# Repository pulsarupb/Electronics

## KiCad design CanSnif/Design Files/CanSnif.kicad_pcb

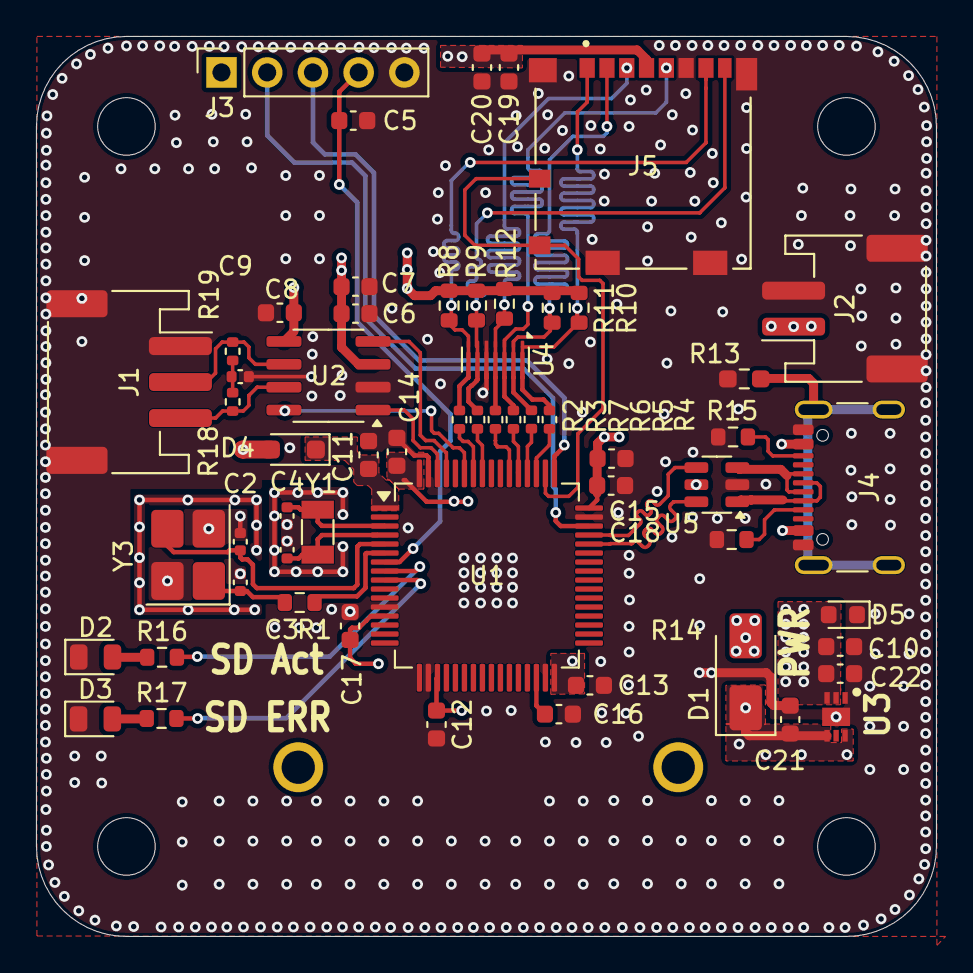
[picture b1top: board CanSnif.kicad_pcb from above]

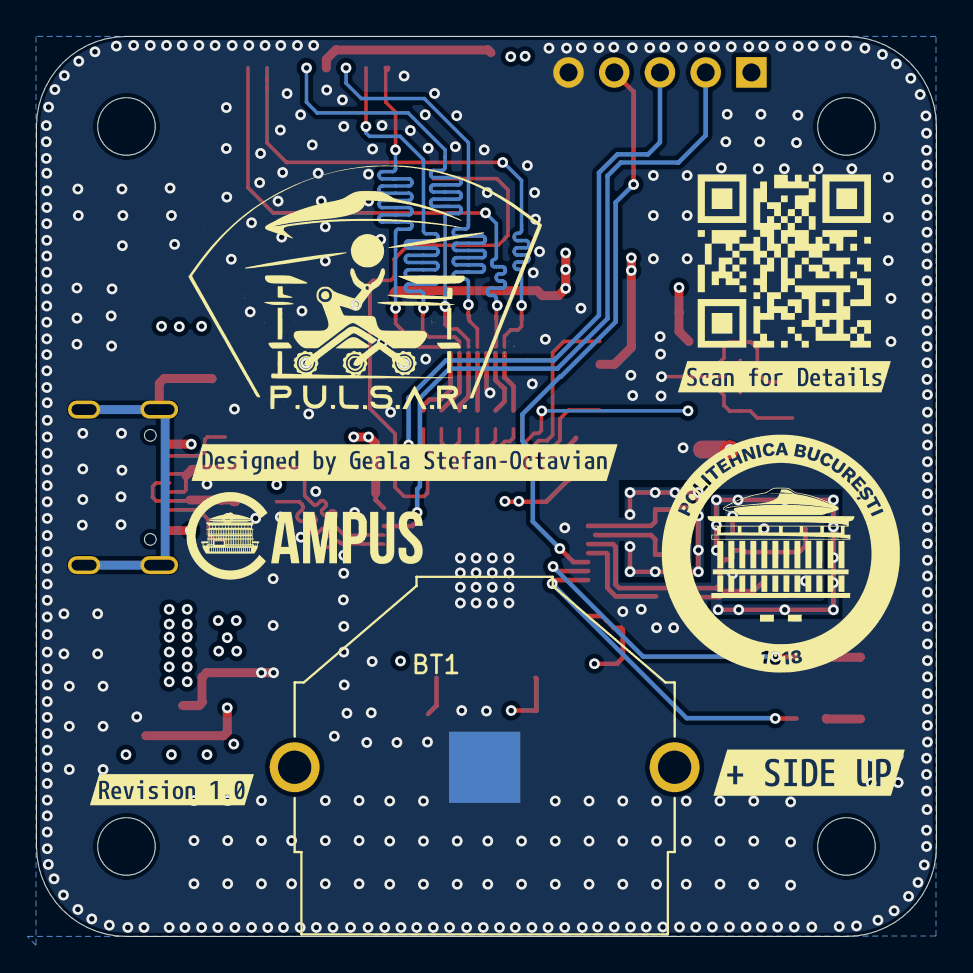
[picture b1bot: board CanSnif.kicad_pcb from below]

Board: 4 copper layers, 50.0 x 50.0 mm, 63 parts (5 on the bottom side), 44 nets.

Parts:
BT1: 3003; BAT_3003
C1, C2: 10pF; C_0402_1005Metric
C3, C4: 14pF; C_0402_1005Metric
C5, C6, C8, C11, C12, C13, C14, C17, C18, C20: 0.1uF; C_0603_1608Metric
C7, C10, C15, C19, C21, C22: 10uF; C_0603_1608Metric
C9: 4.7nF; C_0402_1005Metric
C16: 4.7uF; C_0603_1608Metric
D1: SS32; D_SMA
D2: SD Error; LED_0805_2012Metric
D3: SD Activity; LED_0805_2012Metric
D4: 1N5819WS; D_SOD-323_HandSoldering
D5: Red; LED_0603_1608Metric
J1: JST_XH; JST_PH_S3B-PH-SM4-TB_1x03-1MP_P2.00mm_Horizontal
J2: JST_XH; JST_PH_S2B-PH-SM4-TB_1x02-1MP_P2.00mm_Horizontal
J3: Pin_Header; PinSocket_1x05_P2.54mm_Vertical
J4: USB_C_Receptacle_USB2.0_16P; USB_C_Receptacle_GCT_USB4105-xx-A_16P_TopMnt_Horizontal
J5: 104031-0811; MOLEX_104031-0811
R1: 0; R_0603_1608Metric
R2, R3, R4, R5, R6, R7: 22; R_0402_1005Metric
R8, R9, R10, R11, R12: 47K; R_0603_1608Metric
R13: 200K; R_0603_1608Metric_Pad0.98x0.95mm_HandSolder
R14, R15: 5.1K; R_0603_1608Metric
R16, R17: 330; R_0603_1608Metric
R18, R19: 60; R_0402_1005Metric
U1: STM32U575RGT6; LQFP-64_10x10mm_P0.5mm
U2: TJA1051T-3; SOIC-8_3.9x4.9mm_P1.27mm
U3: LDL212PV33R; SON50P200X200X80-7N-D
U4: TPD6E05U06RVZ; Texas_R-PUSON-N14
U5: USBLC6-2SC6; SOT-23-6
Y1: 32.768KHz; Crystal_SMD_3215-2Pin_3.2x1.5mm
Y3: 16MHz; Crystal_SMD_3225-4Pin_3.2x2.5mm_HandSoldering
kibuzzard-69AC8A77: G***; kibuzzard-69AC8A77
kibuzzard-69AC84C5: G***; kibuzzard-69AC84C5
kibuzzard-69AC87A2: G***; kibuzzard-69AC87A2
kibuzzard-69AC8543: G***; kibuzzard-69AC8543

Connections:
+3V3: C8.1, C10.1, C12.1, C13.1, C14.1, C15.1, C17.1, C18.1, C19.2, C20.2, C22.1, D5.2, J3.1, J5.4 (VDD), R8.2, R9.2, R10.2, R11.2, R12.1, U1.13 (VDDA), U1.19 (VDD), U1.32 (VDD), U1.48 (VDDUSB), U1.64 (VDD), U2.5 (VIO), U3.2 (ADJ/SENSE), U3.3 (VOUT)
+5V: C6.2, C7.2, C21.1, D1.1 (K), U2.3 (VCC), U3.4 (VIN), U3.6 (EN)
CANH: J1.3, R18.2, U2.7 (CANH)
CANL: J1.2, R19.1, U2.6 (CANL)
CR2032: C11.2, D4.1 (K), U1.1 (VBAT)
FDCAN_RX: U1.61 (PB8), U2.4 (RXD)
FDCAN_S: U1.59 (PB7), U2.8 (S)
FDCAN_TX: U1.62 (PB9), U2.1 (TXD)
GND: BT1.N, C1.2, C2.2, C3.1, C4.1, C5.2, C6.1, C7.1, C8.2, C9.2, C10.2, C11.1, C12.2, C13.2, C14.2, C15.2, C16.2, C17.2, C18.2, C19.1, C20.1, C21.2, C22.2, D2.1 (K), D3.1 (K), D5.1, J1.1, J1.MP, J2.2, J2.MP, J3.5, J4.A1 (GND), J4.A12 (GND), J4.B1 (GND), J4.B12 (GND), J5.6 (VSS), J5.G1 (GND), J5.G2 (GND), J5.G3 (GND), J5.G4 (GND), R13.2, R14.2, R15.2, U1.12 (VSSA), U1.18 (VSS), U1.31 (VSS), U1.47 (VSS), U1.63 (VSS), U2.2 (GND), U3.1 (GND), U3.7 (EP), U4.5 (GND), U4.10 (GND), U5.2 (GND), Y3.2, Y3.4
NRST: C5.1, J3.4, U1.7 (NRST)
unnamed: C1.1, R1.1, Y3.1
unnamed: C9.1, R18.1, R19.2
unnamed: D1.2 (A), J2.1, J4.A4 (VBUS), J4.A9 (VBUS), J4.B4 (VBUS), J4.B9 (VBUS), U5.5 (VBUS)
unnamed: D2.2 (A), R16.1
unnamed: D3.2 (A), R17.1
unnamed: BT1.P1, BT1.P2, D4.2 (A)
unnamed: J4.A5 (CC1), R14.1
unnamed: J4.B5 (CC2), R15.1
unnamed: J4.A6 (D+), J4.B6 (D+), U5.3 (I/O2)
unnamed: J4.A7 (D-), J4.B7 (D-), U5.1 (I/O1)
unnamed: J4.S1 (SHIELD), R13.1
unnamed: J5.2 (CD/DAT3), R5.1, R11.1, U4.13 (D1-)
unnamed: J5.5 (CLK), R6.2
unnamed: J5.3 (CMD), R7.2, R12.2
unnamed: J5.8 (DAT1), R3.1, R9.1
unnamed: J5.1 (DAT2), R4.1, R10.1
unnamed: R16.2, U1.8 (PC0)
unnamed: R17.2, U1.9 (PC1)
unnamed: C4.2, U1.3 (PC14), Y1.2
unnamed: C3.2, U1.4 (PC15), Y1.1
unnamed: C2.1, U1.5 (PH0), Y3.3
unnamed: R1.2, U1.6 (PH1)
unnamed: C16.1, U1.30 (VCAP)
SDMMC1_CK: R6.1, U1.53 (PC12), U4.3 (NC), U4.12 (D2+)
SDMMC1_CMD: R7.1, U1.54 (PD2), U4.4 (NC), U4.11 (D2-)
SDMMC1_DAT0: J5.7 (DAT0), R2.2, R8.1, U1.58 (PB6), U4.7 (NC), U4.8 (D3-)
SDMMC1_DAT1: R3.2, U1.57 (PB5), U4.6 (NC), U4.9 (D3+)
SDMMC1_DAT2: R2.1, R4.2, U1.51 (PC10), U4.1 (NC), U4.14 (D1+)
SDMMC1_DAT3: R5.2, U1.52 (PC11), U4.2 (NC)
SDMMC1_SW: J5.9 (SW-1), J5.10 (SW-2), U1.50 (PA15)
SWDCLK: J3.3, U1.49 (PA14)
SWDIO: J3.2, U1.46 (PA13)
USB_OTG_FS_D+: U1.45 (PA12), U5.4 (I/O2)
USB_OTG_FS_D-: U1.44 (PA11), U5.6 (I/O1)

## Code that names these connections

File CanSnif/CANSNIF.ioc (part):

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Mcu.Name=STM32U575RGTx
Mcu.Package=LQFP64
Mcu.UserName=STM32U575RGTx
PA11.Mode=Device_Only
PA11.Signal=USB_OTG_FS_DM
PA12.Mode=Device_Only
PA12.Signal=USB_OTG_FS_DP
PA13\ (JTMS/SWDIO).Mode=Serial_Wire
PA13\ (JTMS/SWDIO).Signal=DEBUG_JTMS-SWDIO
PA14\ (JTCK/SWCLK).Mode=Serial_Wire
PA14\ (JTCK/SWCLK).Signal=DEBUG_JTCK-SWCLK
PA15\ (JTDI).GPIOParameters=GPIO_Label
PA15\ (JTDI).GPIO_Label=SDMMC1_DET
PA15\ (JTDI).Signal=GPIO_Input
PB5.Signal=GPIO_Input
PB6.Signal=GPIO_Input
PB7.GPIOParameters=GPIO_Label
PB7.GPIO_Label=FDCAN_S
PB7.Signal=GPIO_Output
PB8.Mode=FDCAN_Activate
PB8.Signal=FDCAN1_RX
PB9.Mode=FDCAN_Activate
PB9.Signal=FDCAN1_TX
PC0.GPIOParameters=GPIO_Label
PC0.GPIO_Label=SD_Error
PC0.Signal=GPIO_Output
PC1.GPIOParameters=GPIO_Label
PC1.GPIO_Label=SD_Activity
PC1.Signal=GPIO_Output
PC10.Mode=SD_4_bits_Wide_bus
PC10.Signal=SDMMC1_D2
PC11.Mode=SD_4_bits_Wide_bus
PC11.Signal=SDMMC1_D3
PC12.Mode=SD_4_bits_Wide_bus
PC12.Signal=SDMMC1_CK
PC14-OSC32_IN\ (PC14).Mode=LSE-External-Oscillator
PC14-OSC32_IN\ (PC14).Signal=RCC_OSC32_IN
PC15-OSC32_OUT\ (PC15).Mode=LSE-External-Oscillator
PC15-OSC32_OUT\ (PC15).Signal=RCC_OSC32_OUT
PC8.Mode=SD_4_bits_Wide_bus
PC8.Signal=SDMMC1_D0
PC9.Mode=SD_4_bits_Wide_bus
PC9.Signal=SDMMC1_D1
PD2.Mode=SD_4_bits_Wide_bus
PD2.Signal=SDMMC1_CMD
PH0-OSC_IN\ (PH0).Mode=HSE-External-Oscillator
PH0-OSC_IN\ (PH0).Signal=RCC_OSC_IN
PH1-OSC_OUT\ (PH1).Mode=HSE-External-Oscillator
PH1-OSC_OUT\ (PH1).Signal=RCC_OSC_OUT
RCC.HSE_VALUE=16000000
RCC.SYSCLKFreq_VALUE=48000000
board=custom

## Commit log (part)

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2026-02-15 Intial commit for Controlled Current Source Buck Test
2026-03-07 CanSniff and prerequisites added
2026-03-07 Updated the Silkscreen
2026-03-07 added battery orientation warning
2026-03-07 structure update
2026-03-08 Finish
